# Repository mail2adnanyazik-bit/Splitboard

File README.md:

# Splitboard - a custom, built from scratch wireless corne split keyboard. Built for Stardance, to qualify for Outpost.

Splitboard is a wireless split keyboard built by ME - Panda (also known as Adnan)

You see, my dad has had a dygma raise split keyboard since like 4 years, and i thought it looked REALLY cool, and wanted to get one -
till i saw the price - the thing was whopping **_200 DOLLARS_** ! So i thought to myself - why not build one myself ?

By the time this event rolled around, i was already getting tired of my very *anti-*ergonomic apple magic keyboard, and thought
that this project would be perfect, expecially cause of the experience with keyboards i got from the Hackpad mission.

That is how the **Splitboard** was born.

## Components :

Since this keyboard was made completely from scratch, i first will tell you whats its made of :

The Split Keyboard has 2 halves, with each having :

- 21 Keys (3x6 matrix with 3 thumb keys) - in the classic Corne layout
- One OLED (blue, since thats myt fav color)
- A supermini nrf52840 microcontroller - this is a cheap nice ! nano v2 clone, a wireless chip made excpecially with keyboards in mind
- A 110 mAh Battery (should last weeks with my setup)

So this is the Schematic with all mentioned components :

## Schematic :

As you can see, i dont like wires :D

## PCB :

left side :

right side :

Although the initial plan was to make a _reversible_ PCB that i would just turn 180 degrees, i decided to make my keyboard not symmetric - which means i cant just turn it around, instead i have to make two seperate PCB's

## Case :

You can view it interactively on OnShape in your Browser ! : https://cad.onshape.com/documents/4401902cdc607732e38adc1c/w/b44e538c7538a5811b6e646c/e/3efcd232ff04d945eef59e16?renderMode=0&uiState=6a440a2cf26d36c1903a4b4f

For the case, i decided to use just two parts :

- ### A Case Bottom :

  This just holds the PCB and components for my keyboard

- ### A Top Plate :
  This will be screwed on to the base, and has holes for the components that need to look out to poke out

## Assembly :

There will be a such Bottom and Top for both halves of the keyboard, and it will then be assembled like this :

Then Keycaps will be pressed on to the switches.

This will be done on both sides :

In the end it will look like this :

## Firmware :

Because i had to make the firmware extremely fast for outpost, im just making a completely boring, standard corne keyboard firmware with ZMK

## Costs (BOM) :

I will buy everything except PCB from Aliexpress

2x supermini nrf52840 : 15 $
2x 110 mAh LiPo battery : 5 $
1N4148 SMD Diodes : 2 $
Kailh MX Hotswap sockets : ~ 7 $
42 x Cherry MX Switches : ~ 40 $
42 x Cherry MX Keycaps : 25 $
2 x 0.91" OLED Display : 6$
4.7kΩ SMD resistors : 1 $
100kΩ SMD resistors : 1$
SPST slide switches : 0.50 $
JST PH 2.0 2-pin connector (for battery) : 1 $
M2 standoffs + screws kit : 2 $
8mm self-adhesive bumpons (less glide) : 2 $
PCB from JLCPCB : 20 $
Shipping (Aliexpress and JLCPCB) : 15 $

**==IMPORTANT==** : This BOM is NOT accurate ! Check the actual BOM.csv file in the main branch

Total : ~ 115$

I would add another 15 - 20 dollar buffer since something is bound to go wrong, so in the end it would be around 160 dollars.

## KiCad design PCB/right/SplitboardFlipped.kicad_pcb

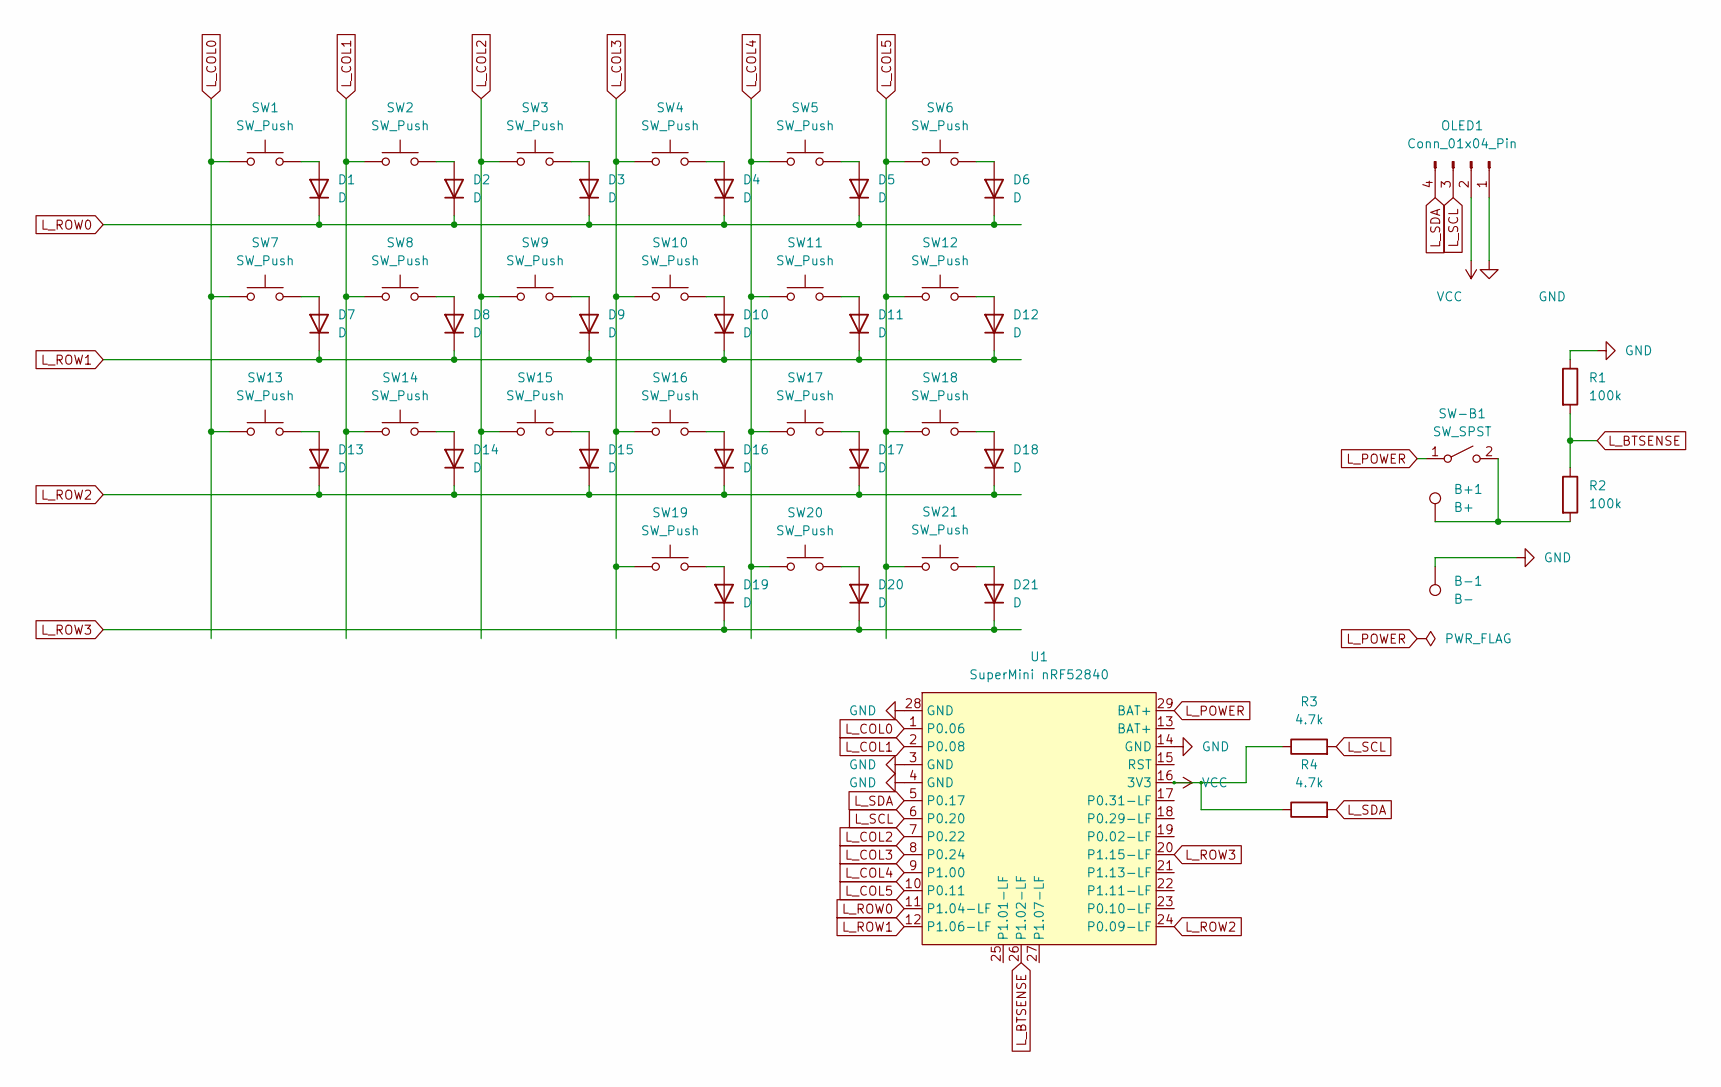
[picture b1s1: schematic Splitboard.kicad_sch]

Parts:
B+1: B+; TestPoint_Pad_1.5x1.5mm
B-1: B-; TestPoint_Pad_1.5x1.5mm
D1, D2, D3, D4, D5, D6, D7, D8, D9, D10, D11, D12, D13, D14, D15, D16, D17, D18, D19, D20, D21: D; D_SOD-123
OLED1: Conn_01x04_Pin; SSD1306-0.91-OLED-4pin-128x32
R1, R2: 100k; R_0603_1608Metric
R3, R4: 4.7k; R_0603_1608Metric
SW1, SW2, SW3, SW4, SW5, SW6, SW7, SW8, SW9, SW10, SW11, SW12, SW13, SW14, SW15, SW16, SW17, SW18, SW19, SW20, SW21: SW_Push; Kailh_socket_MX_reversible
SW-B1: SW_SPST; SW_DIP_SPSTx01_Slide_9.78x4.72mm_W8.61mm_P2.54mm
U1: SuperMini nRF52840; supermini

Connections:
GND: B-1.1, OLED1.1, R1.1, U1.3 (GND), U1.4 (GND), U1.14 (GND), U1.28 (GND)
L_BTSENSE: R1.2, R2.1, U1.26 (P1.02-LF)
L_COL0: SW1.1, SW7.1, SW13.1, U1.1 (P0.06)
L_COL1: SW2.1, SW8.1, SW14.1, U1.2 (P0.08)
L_COL2: SW3.1, SW9.1, SW15.1, U1.7 (P0.22)
L_COL3: SW4.1, SW10.1, SW16.1, SW19.1, U1.8 (P0.24)
L_COL4: SW5.1, SW11.1, SW17.1, SW20.1, U1.9 (P1.00)
L_COL5: SW6.1, SW12.1, SW18.1, SW21.1, U1.10 (P0.11)
L_POWER: SW-B1.1 (A), U1.29 (BAT+)
L_ROW0: D1.1 (K), D2.1 (K), D3.1 (K), D4.1 (K), D5.1 (K), D6.1 (K), U1.11 (P1.04-LF)
L_ROW1: D7.1 (K), D8.1 (K), D9.1 (K), D10.1 (K), D11.1 (K), D12.1 (K), U1.12 (P1.06-LF)
L_ROW2: D13.1 (K), D14.1 (K), D15.1 (K), D16.1 (K), D17.1 (K), D18.1 (K), U1.24 (P0.09-LF)
L_ROW3: D19.1 (K), D20.1 (K), D21.1 (K), U1.20 (P1.15-LF)
L_SCL: OLED1.3, R3.2, U1.6 (P0.20)
L_SDA: OLED1.4, R4.2, U1.5 (P0.17)
unnamed: D1.2 (A), SW1.2
unnamed: D2.2 (A), SW2.2
unnamed: D3.2 (A), SW3.2
unnamed: D4.2 (A), SW4.2
unnamed: D5.2 (A), SW5.2
unnamed: D6.2 (A), SW6.2
unnamed: D7.2 (A), SW7.2
unnamed: D8.2 (A), SW8.2
unnamed: D9.2 (A), SW9.2
unnamed: D10.2 (A), SW10.2
unnamed: D11.2 (A), SW11.2
unnamed: D12.2 (A), SW12.2
unnamed: D13.2 (A), SW13.2
unnamed: D14.2 (A), SW14.2
unnamed: D15.2 (A), SW15.2
unnamed: D16.2 (A), SW16.2
unnamed: D17.2 (A), SW17.2
unnamed: D18.2 (A), SW18.2
unnamed: D19.2 (A), SW19.2
unnamed: D20.2 (A), SW20.2
unnamed: D21.2 (A), SW21.2
unnamed: B+1.1, R2.2, SW-B1.2 (B)
VCC: OLED1.2, R3.1, R4.1, U1.16 (3V3)

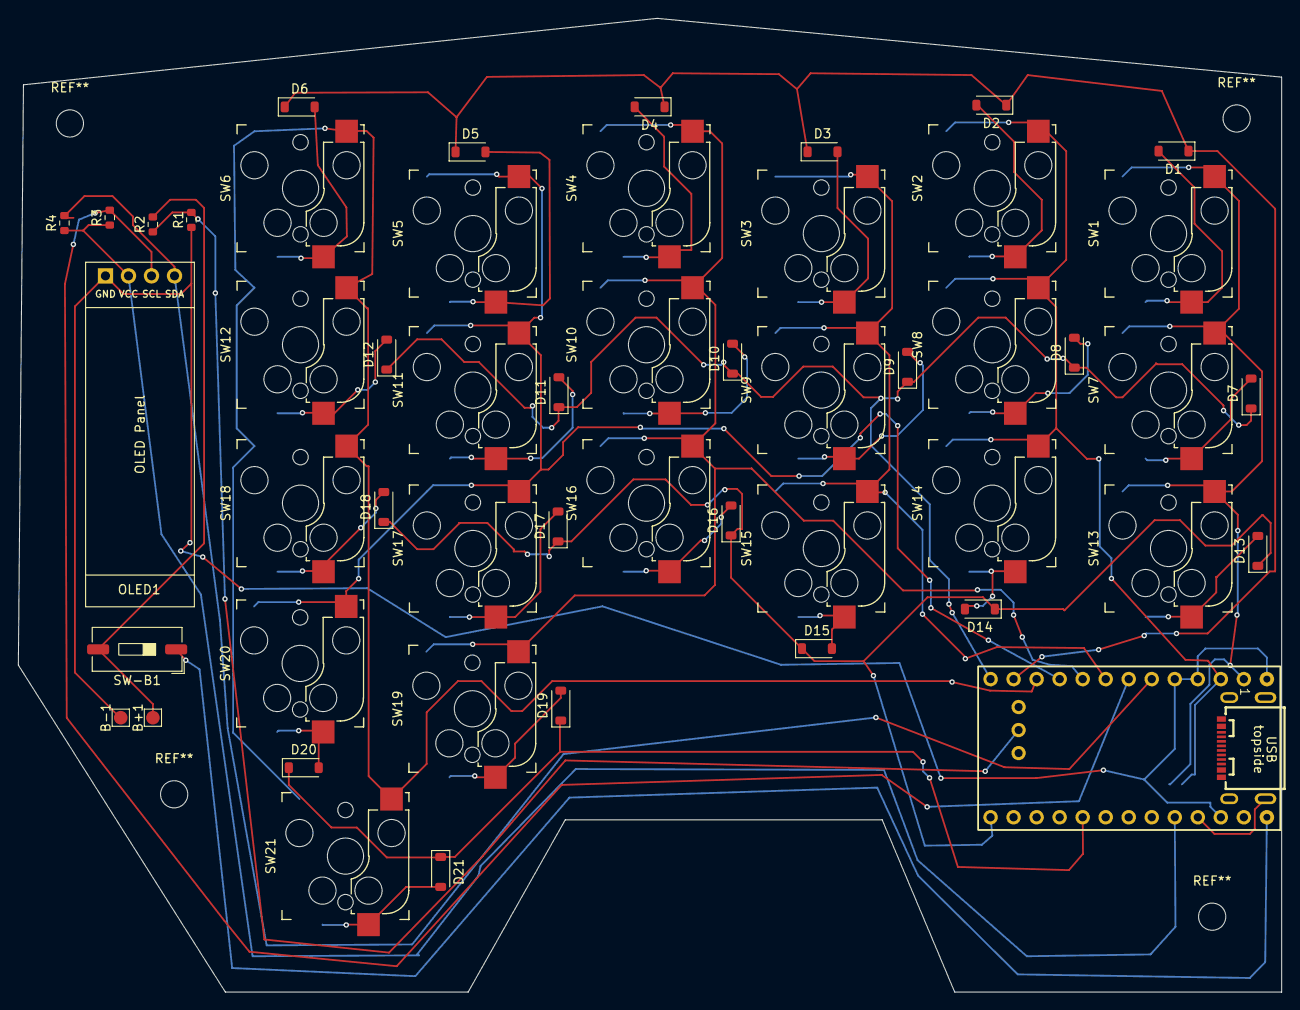
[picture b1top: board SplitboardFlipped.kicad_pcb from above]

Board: 2 copper layers, 139.3 x 107.4 mm, 51 parts (0 on the bottom side), 38 nets.

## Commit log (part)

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2026-06-30 added firmware to README.md
2026-06-30 adjust according to feedback
2026-06-30 adjust BOM to use cheaper components
2026-06-30 add OnShape link to README
2026-06-30 add shipping, fix price mismatch
